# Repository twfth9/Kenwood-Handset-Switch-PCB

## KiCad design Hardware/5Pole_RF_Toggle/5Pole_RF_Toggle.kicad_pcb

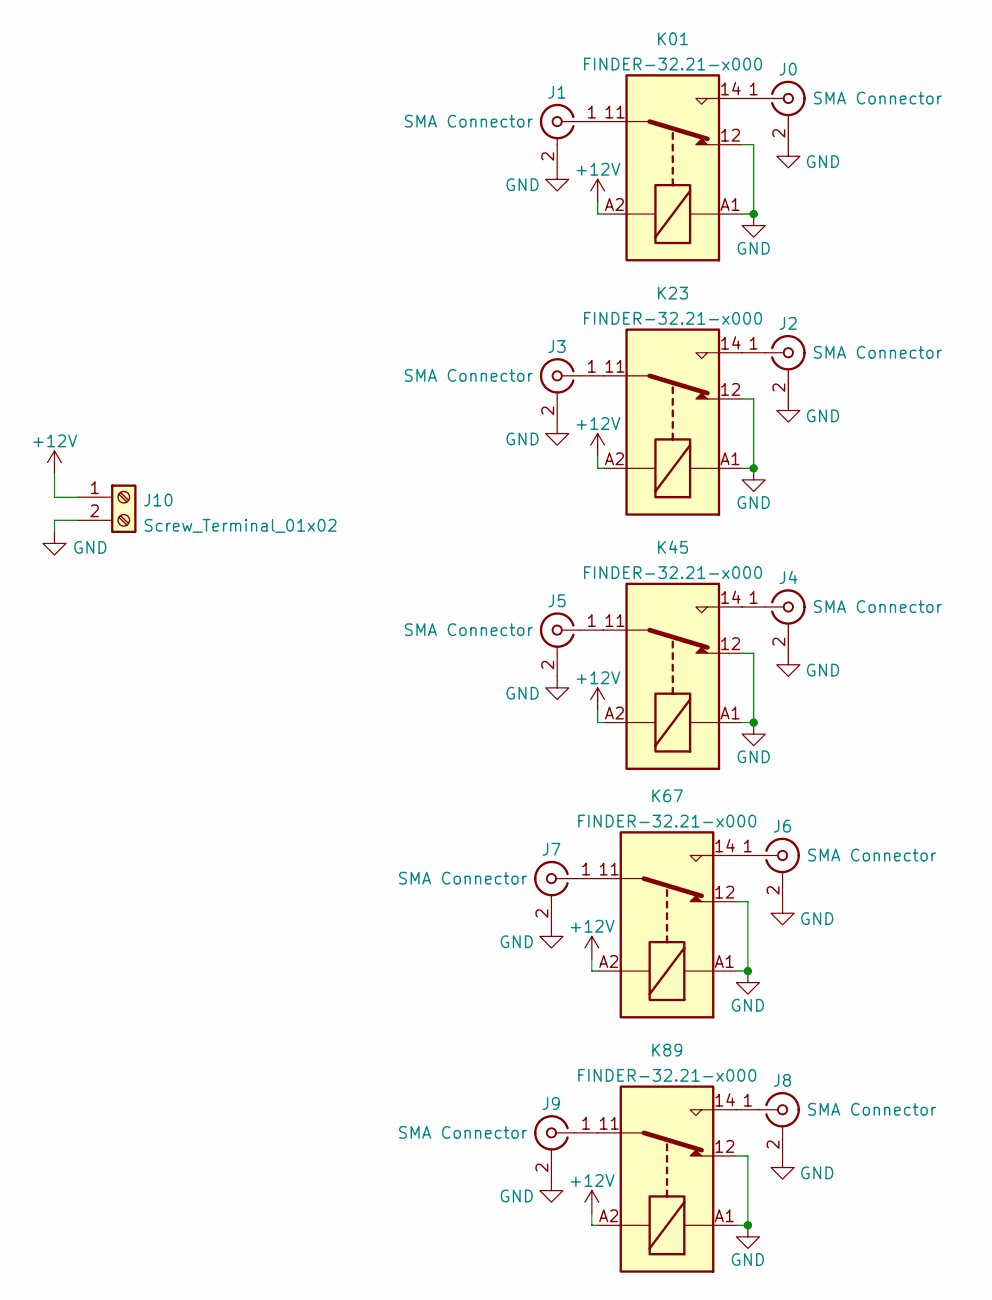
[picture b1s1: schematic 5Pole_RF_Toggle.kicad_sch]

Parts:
J0, J1, J2, J3, J4, J5, J6, J7, J8, J9: SMA Connector; SMA_Amphenol_132134-11_Vertical
J10: Screw_Terminal_01x02; TerminalBlock_Phoenix_MKDS-1,5-2_1x02_P5.00mm_Horizontal
K01, K23, K45, K67, K89: FINDER-32.21-x000; Relay_SPDT_Finder_32.21-x000

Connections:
+12V: J10.1, K01.A2, K23.A2, K45.A2, K67.A2, K89.A2
GND: J0.2 (Ext), J1.2 (Ext), J2.2 (Ext), J3.2 (Ext), J4.2 (Ext), J5.2 (Ext), J6.2 (Ext), J7.2 (Ext), J8.2 (Ext), J9.2 (Ext), J10.2, K01.12, K01.A1, K23.12, K23.A1, K45.12, K45.A1, K67.12, K67.A1, K89.12, K89.A1
unnamed: J0.1 (In), K01.14
unnamed: J1.1 (In), K01.11
unnamed: J2.1 (In), K23.14
unnamed: J3.1 (In), K23.11
unnamed: J4.1 (In), K45.14
unnamed: J5.1 (In), K45.11
unnamed: J6.1 (In), K67.14
unnamed: J7.1 (In), K67.11
unnamed: J8.1 (In), K89.14
unnamed: J9.1 (In), K89.11

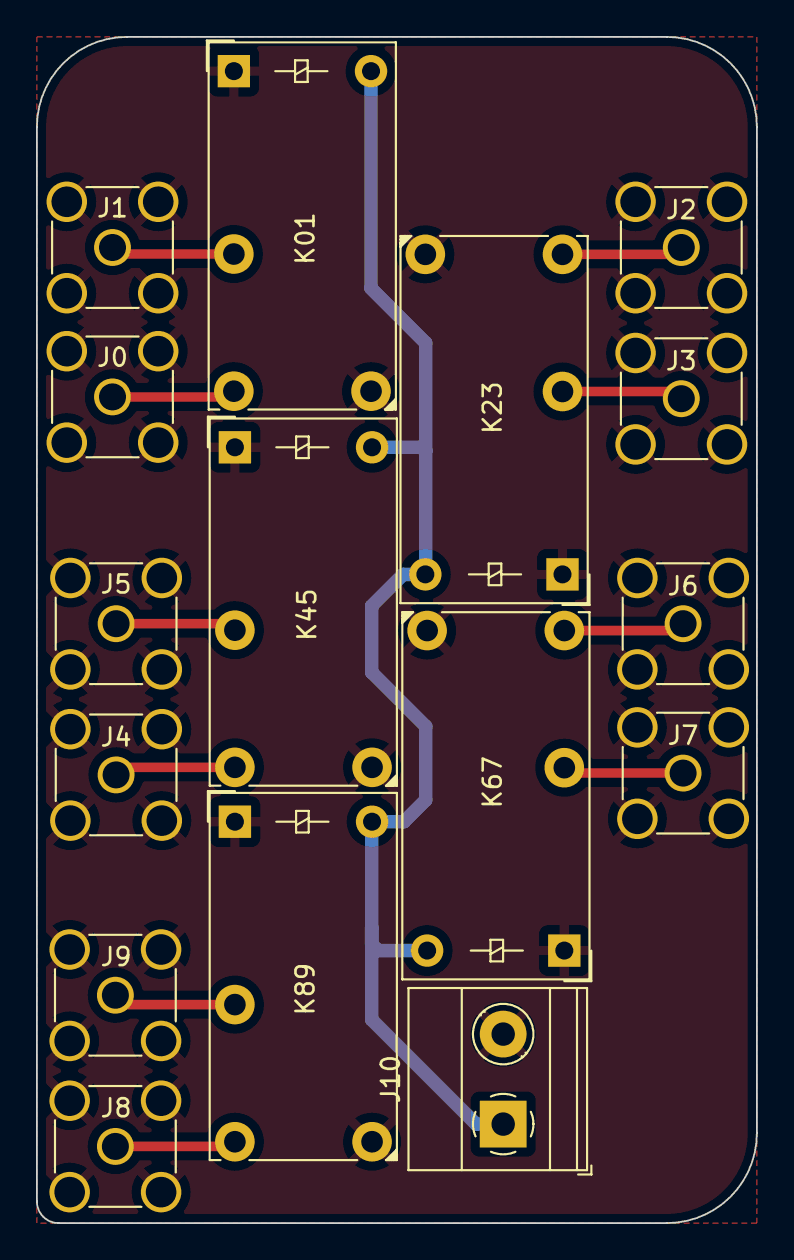
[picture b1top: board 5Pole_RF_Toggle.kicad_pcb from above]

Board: 2 copper layers, 40.0 x 65.9 mm, 16 parts (0 on the bottom side), 12 nets.

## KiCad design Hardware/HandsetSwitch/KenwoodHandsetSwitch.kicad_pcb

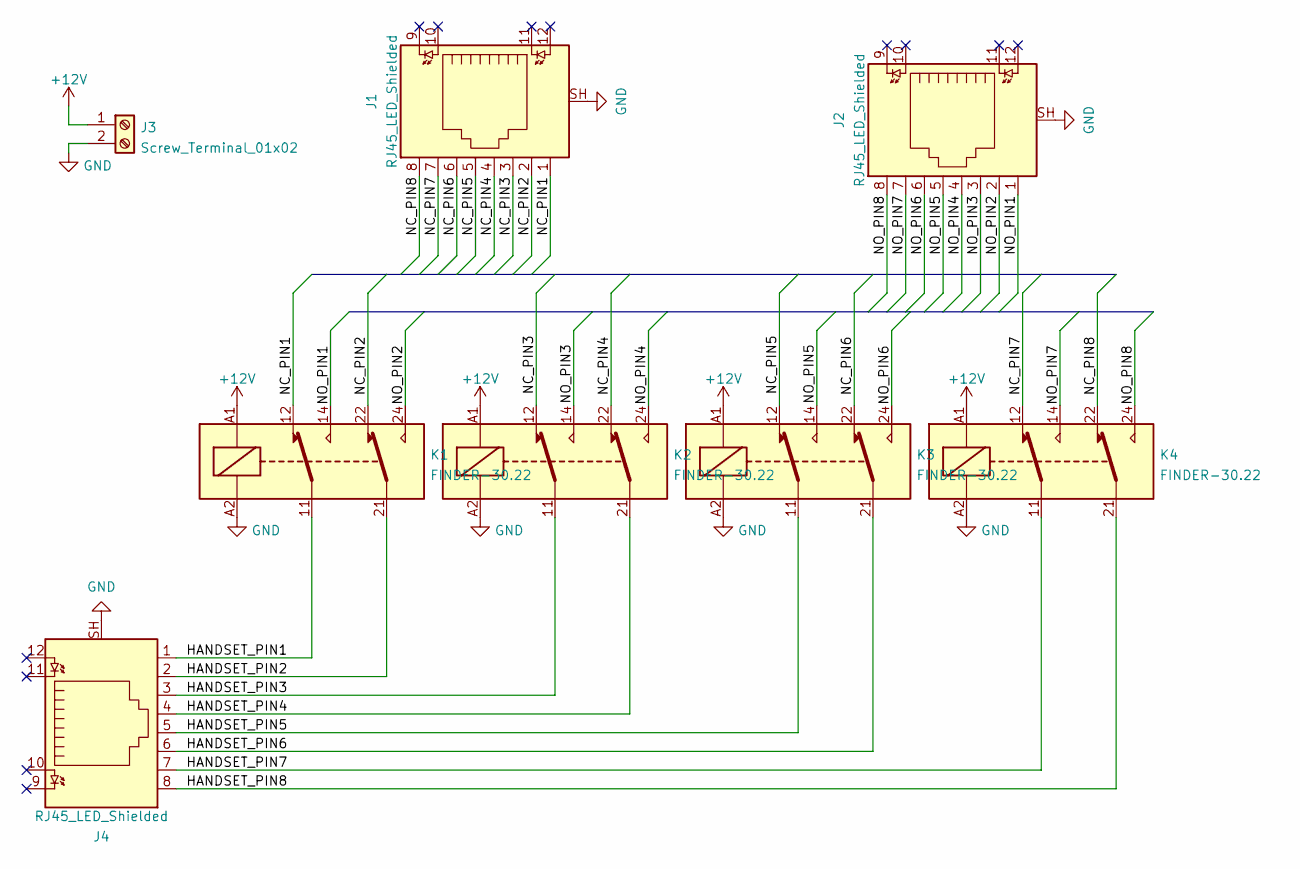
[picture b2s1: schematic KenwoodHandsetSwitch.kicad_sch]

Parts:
J1, J2, J4: RJ45_LED_Shielded; RJ45_BEL_SS74301-00x_Vertical
J3: Screw_Terminal_01x02; TerminalBlock_Phoenix_MKDS-1,5-2_1x02_P5.00mm_Horizontal
K1, K2, K3, K4: FINDER-30.22; Relay_DPDT_Finder_30.22

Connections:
+12V: J3.1, K1.A1, K2.A1, K3.A1, K4.A1
/HANDSET_PIN1: J4.1, K1.11
/HANDSET_PIN2: J4.2, K1.21
/HANDSET_PIN3: J4.3, K2.11
/HANDSET_PIN4: J4.4, K2.21
/HANDSET_PIN5: J4.5, K3.11
/HANDSET_PIN6: J4.6, K3.21
/HANDSET_PIN7: J4.7, K4.11
/HANDSET_PIN8: J4.8, K4.21
/NC_PIN1: J1.1, K1.12
/NC_PIN2: J1.2, K1.22
/NC_PIN3: J1.3, K2.12
/NC_PIN4: J1.4, K2.22
/NC_PIN5: J1.5, K3.12
/NC_PIN6: J1.6, K3.22
/NC_PIN7: J1.7, K4.12
/NC_PIN8: J1.8, K4.22
/NO_PIN1: J2.1, K1.14
/NO_PIN2: J2.2, K1.24
/NO_PIN3: J2.3, K2.14
/NO_PIN4: J2.4, K2.24
/NO_PIN5: J2.5, K3.14
/NO_PIN6: J2.6, K3.24
/NO_PIN7: J2.7, K4.14
/NO_PIN8: J2.8, K4.24
GND: J1.SH, J2.SH, J3.2, J4.SH, K1.A2, K2.A2, K3.A2, K4.A2

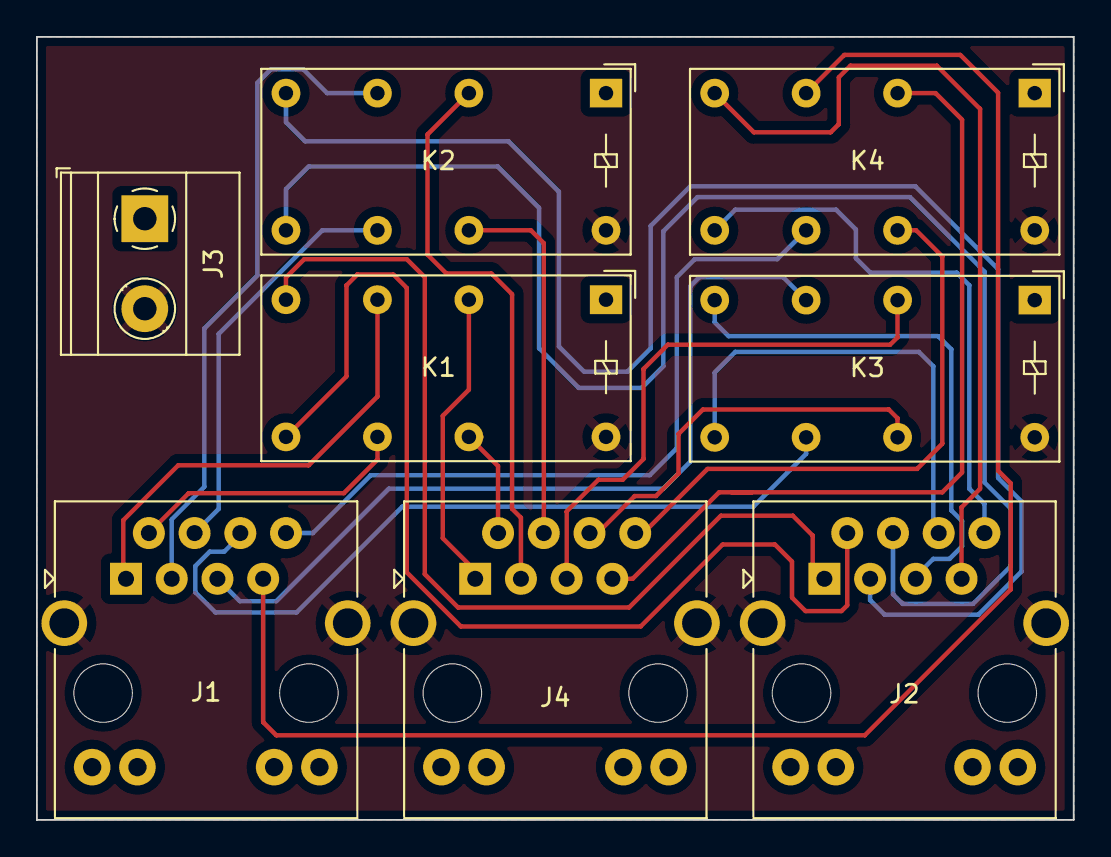
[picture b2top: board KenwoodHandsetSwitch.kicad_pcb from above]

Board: 2 copper layers, 57.6 x 43.5 mm, 8 parts (0 on the bottom side), 26 nets.

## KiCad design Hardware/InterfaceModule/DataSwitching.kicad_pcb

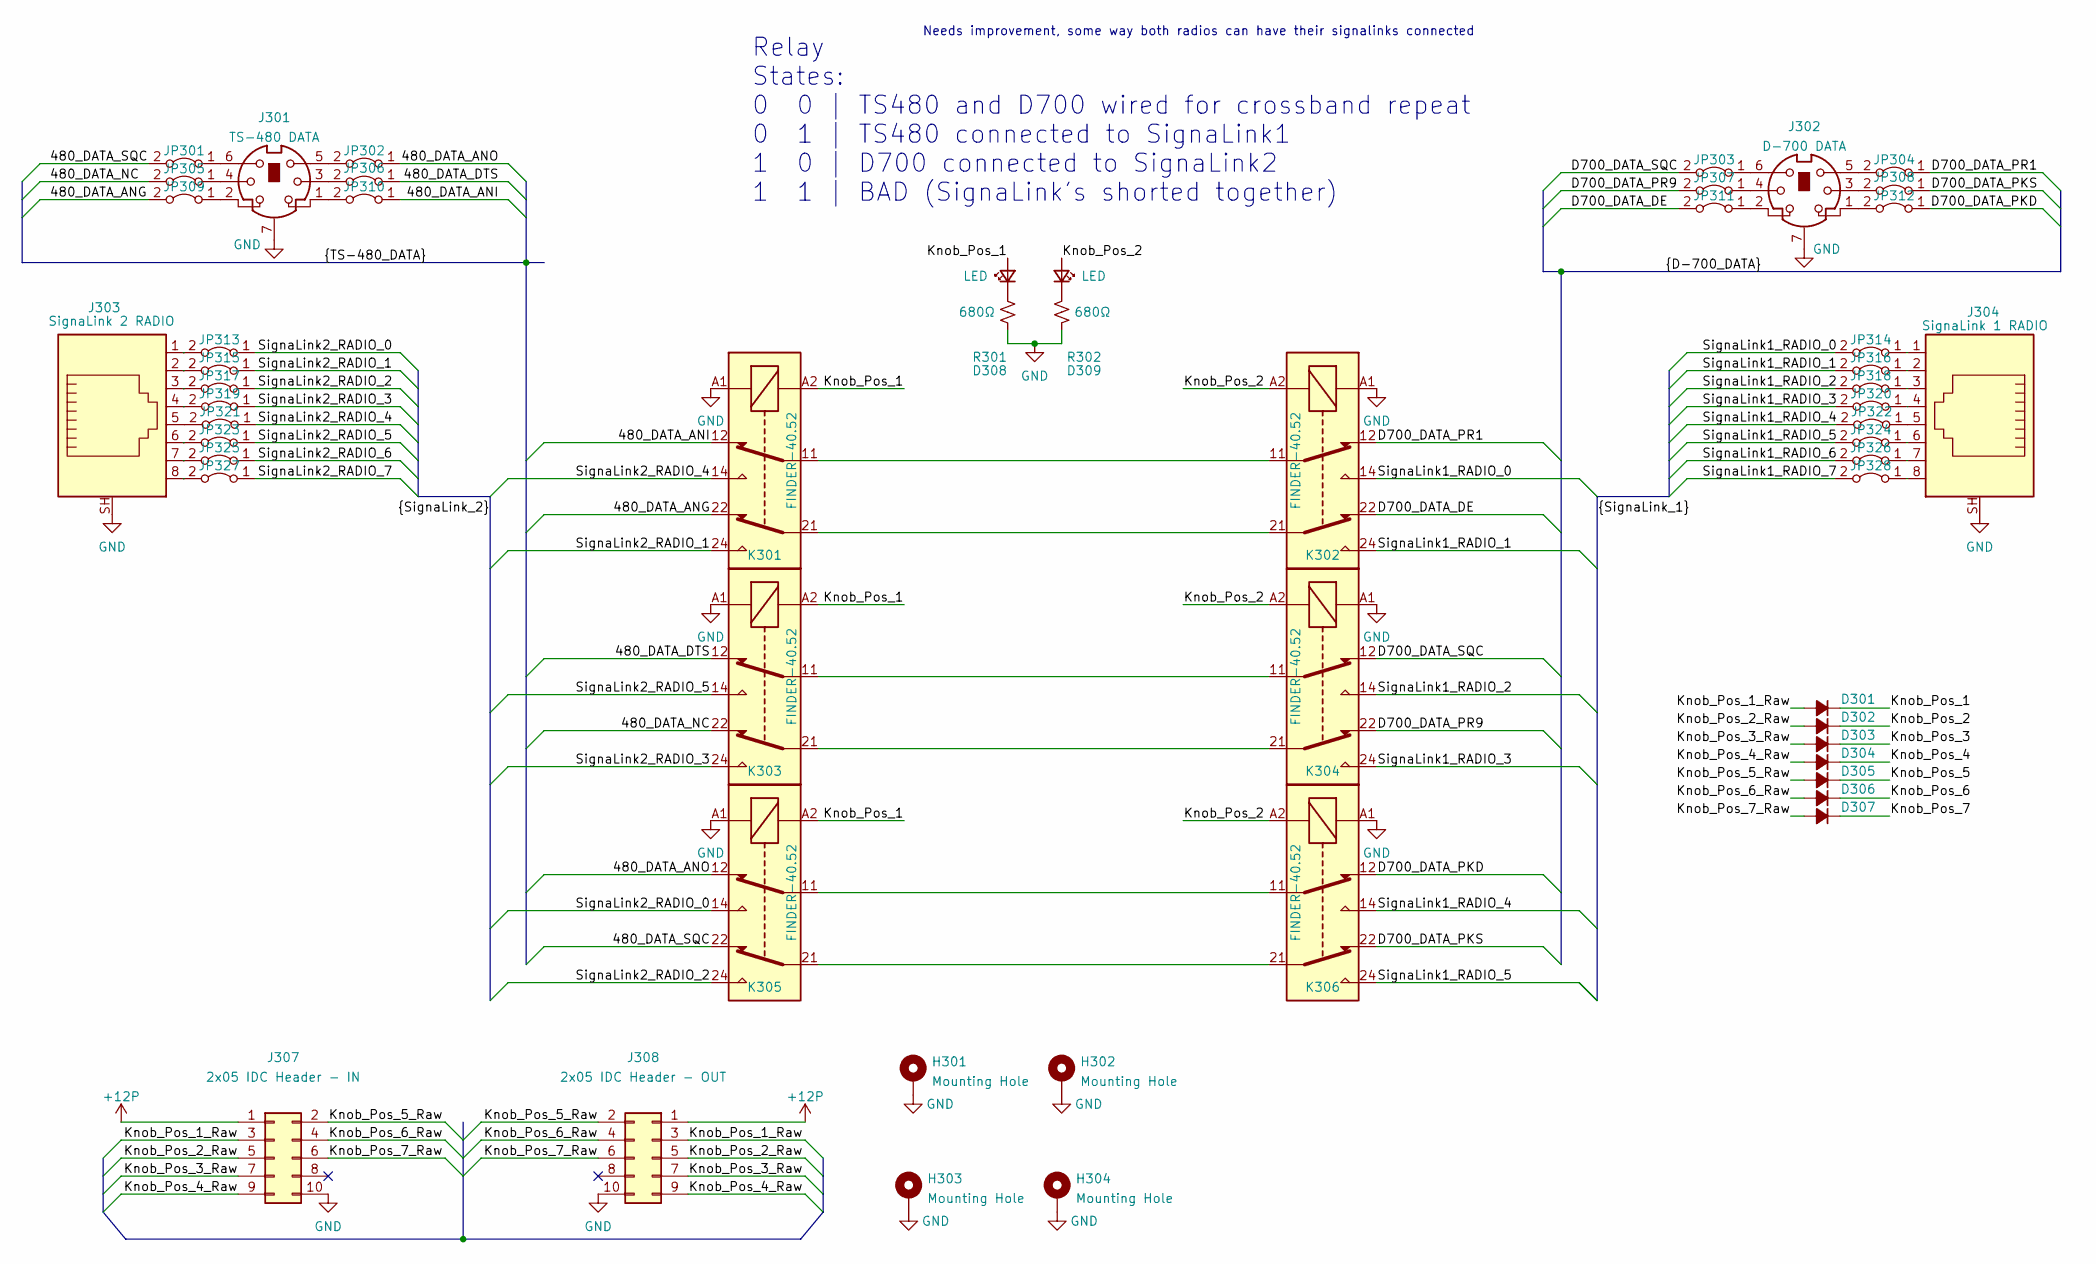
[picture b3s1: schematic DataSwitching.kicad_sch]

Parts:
D301, D302, D303, D304, D305, D306, D307: D_Small_Filled; D_A-405_P2.54mm_Vertical_AnodeUp
D308, D309: LED; LED_D3.0mm
H301, H302, H303, H304: Mounting Hole; M3_Mounting
J301: TS-480 DATA; Connector_Mini-DIN_Female_6Pin_2rows
J302: D-700 DATA; Connector_Mini-DIN_Female_6Pin_2rows
J303: SignaLink 2 RADIO; Mystery_RJ45
J304: SignaLink 1 RADIO; Mystery_RJ45
J307: 2x05 IDC Header - IN; IDC-Header_2x05_P2.54mm_Vertical
J308: 2x05 IDC Header - OUT; IDC-Header_2x05_P2.54mm_Vertical
JP301, JP302, JP303, JP304, JP305, JP306, JP307, JP308, JP309, JP310, JP311, JP312, JP313, JP314, JP315, JP316, JP317, JP318, JP319, JP320, JP321, JP322, JP323, JP324, JP325, JP326, JP327, JP328: Jumper_2_Bridged; 1.0mm_Bridge
K301, K302, K303, K304, K305, K306: FINDER-40.52; Relay_DPDT_Finder_30.22
R301, R302: 680Ω; R_Axial_DIN0207_L6.3mm_D2.5mm_P2.54mm_Vertical

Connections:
+12P: J307.1, J308.1
/Data Port Switching/480_DATA_ANG: JP309.2 (B), K301.22
/Data Port Switching/480_DATA_ANI: JP310.1 (A), K301.12
/Data Port Switching/480_DATA_ANO: JP302.1 (A), K305.12
/Data Port Switching/480_DATA_DTS: JP306.1 (A), K303.12
/Data Port Switching/480_DATA_NC: JP305.2 (B), K303.22
/Data Port Switching/480_DATA_SQC: JP301.2 (B), K305.22
/Data Port Switching/D700_DATA_DE: JP311.2 (B), K302.22
/Data Port Switching/D700_DATA_PKD: JP312.1 (A), K306.12
/Data Port Switching/D700_DATA_PKS: JP308.1 (A), K306.22
/Data Port Switching/D700_DATA_PR1: JP304.1 (A), K302.12
/Data Port Switching/D700_DATA_PR9: JP307.2 (B), K304.22
/Data Port Switching/D700_DATA_SQC: JP303.2 (B), K304.12
/Data Port Switching/Knob_Pos_1: D301.1 (K), D308.2 (A), K301.A2, K303.A2, K305.A2
/Data Port Switching/Knob_Pos_1_Raw: D301.2 (A), J307.3, J308.3
/Data Port Switching/Knob_Pos_2: D302.1 (K), D309.2 (A), K302.A2, K304.A2, K306.A2
/Data Port Switching/Knob_Pos_2_Raw: D302.2 (A), J307.5, J308.5
/Data Port Switching/Knob_Pos_3: D303.1 (K)
/Data Port Switching/Knob_Pos_3_Raw: D303.2 (A), J307.7, J308.7
/Data Port Switching/Knob_Pos_4: D304.1 (K)
/Data Port Switching/Knob_Pos_4_Raw: D304.2 (A), J307.9, J308.9
/Data Port Switching/Knob_Pos_5: D305.1 (K)
/Data Port Switching/Knob_Pos_5_Raw: D305.2 (A), J307.2, J308.2
/Data Port Switching/Knob_Pos_6: D306.1 (K)
/Data Port Switching/Knob_Pos_6_Raw: D306.2 (A), J307.4, J308.4
/Data Port Switching/Knob_Pos_7: D307.1 (K)
/Data Port Switching/Knob_Pos_7_Raw: D307.2 (A), J307.6, J308.6
/Data Port Switching/SignaLink1_RADIO_0: JP314.2 (B), K302.14
/Data Port Switching/SignaLink1_RADIO_1: JP316.2 (B), K302.24
/Data Port Switching/SignaLink1_RADIO_2: JP318.2 (B), K304.14
/Data Port Switching/SignaLink1_RADIO_3: JP320.2 (B), K304.24
/Data Port Switching/SignaLink1_RADIO_4: JP322.2 (B), K306.14
/Data Port Switching/SignaLink1_RADIO_5: JP324.2 (B), K306.24
/Data Port Switching/SignaLink1_RADIO_6: JP326.2 (B)
/Data Port Switching/SignaLink1_RADIO_7: JP328.2 (B)
/Data Port Switching/SignaLink2_RADIO_0: JP313.1 (A), K305.14
/Data Port Switching/SignaLink2_RADIO_1: JP315.1 (A), K301.24
/Data Port Switching/SignaLink2_RADIO_2: JP317.1 (A), K305.24
/Data Port Switching/SignaLink2_RADIO_3: JP319.1 (A), K303.24
/Data Port Switching/SignaLink2_RADIO_4: JP321.1 (A), K301.14
/Data Port Switching/SignaLink2_RADIO_5: JP323.1 (A), K303.14
/Data Port Switching/SignaLink2_RADIO_6: JP325.1 (A)
/Data Port Switching/SignaLink2_RADIO_7: JP327.1 (A)
GND: H301.1, H302.1, H303.1, H304.1, J301.7, J302.7, J303.SH, J304.SH, J307.10, J308.10, K301.A1, K302.A1, K303.A1, K304.A1, K305.A1, K306.A1, R301.2, R302.2
unnamed: D308.1 (K), R301.1
unnamed: D309.1 (K), R302.1
unnamed: J301.1, JP310.2 (B)
unnamed: J301.2, JP309.1 (A)
unnamed: J301.3, JP306.2 (B)
unnamed: J301.4, JP305.1 (A)
unnamed: J301.5, JP302.2 (B)
unnamed: J301.6, JP301.1 (A)
unnamed: J302.1, JP312.2 (B)
unnamed: J302.2, JP311.1 (A)
unnamed: J302.3, JP308.2 (B)
unnamed: J302.4, JP307.1 (A)
unnamed: J302.5, JP304.2 (B)
unnamed: J302.6, JP303.1 (A)
unnamed: J303.1, JP313.2 (B)
unnamed: J303.2, JP315.2 (B)
unnamed: J303.3, JP317.2 (B)
unnamed: J303.4, JP319.2 (B)
unnamed: J303.5, JP321.2 (B)
unnamed: J303.6, JP323.2 (B)
unnamed: J303.7, JP325.2 (B)
unnamed: J303.8, JP327.2 (B)
unnamed: J304.1, JP314.1 (A)
unnamed: J304.2, JP316.1 (A)
unnamed: J304.3, JP318.1 (A)
unnamed: J304.4, JP320.1 (A)
unnamed: J304.5, JP322.1 (A)
unnamed: J304.6, JP324.1 (A)
unnamed: J304.7, JP326.1 (A)
unnamed: J304.8, JP328.1 (A)
unnamed: K301.11, K302.11
unnamed: K301.21, K302.21
unnamed: K303.11, K304.11
unnamed: K303.21, K304.21
unnamed: K305.11, K306.11
unnamed: K305.21, K306.21

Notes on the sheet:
Relay States: 0 0 | TS480 and D700 wired for crossband repeat 0 1 | TS480 connected to SignaLink1 1 0 | D700 connected to SignaLink2 1 1 | BAD (SignaLink's shorted together)
Needs improvement, some way both radios can have their signalinks connected

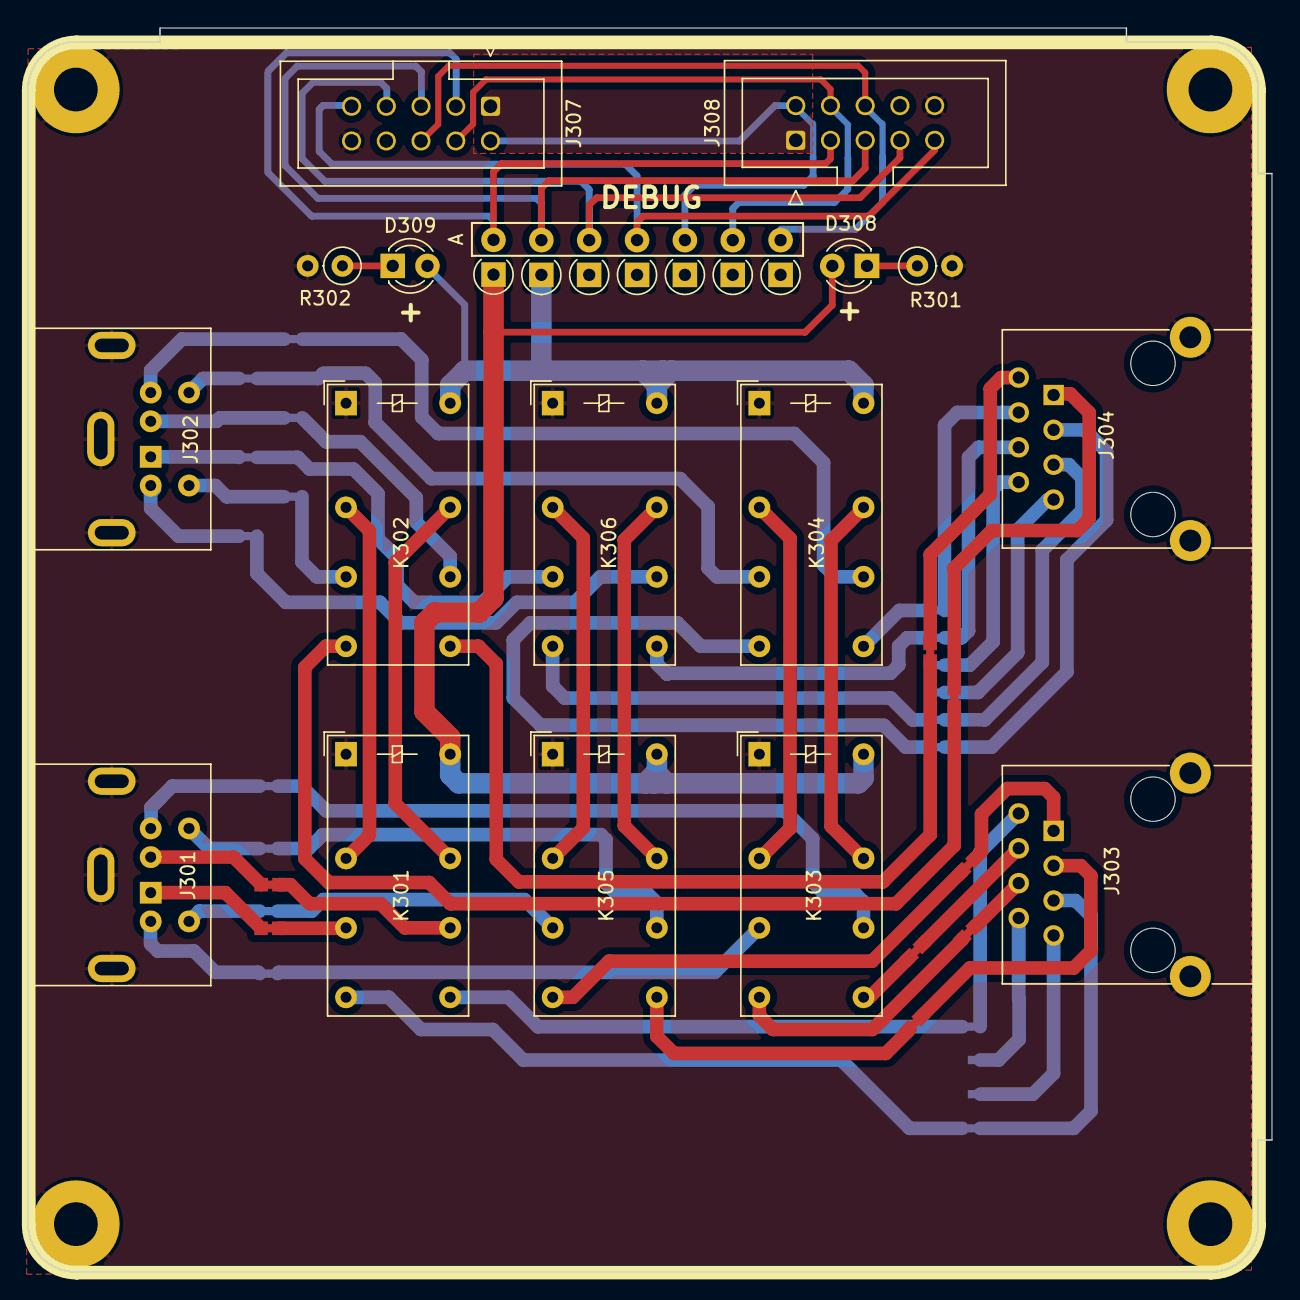
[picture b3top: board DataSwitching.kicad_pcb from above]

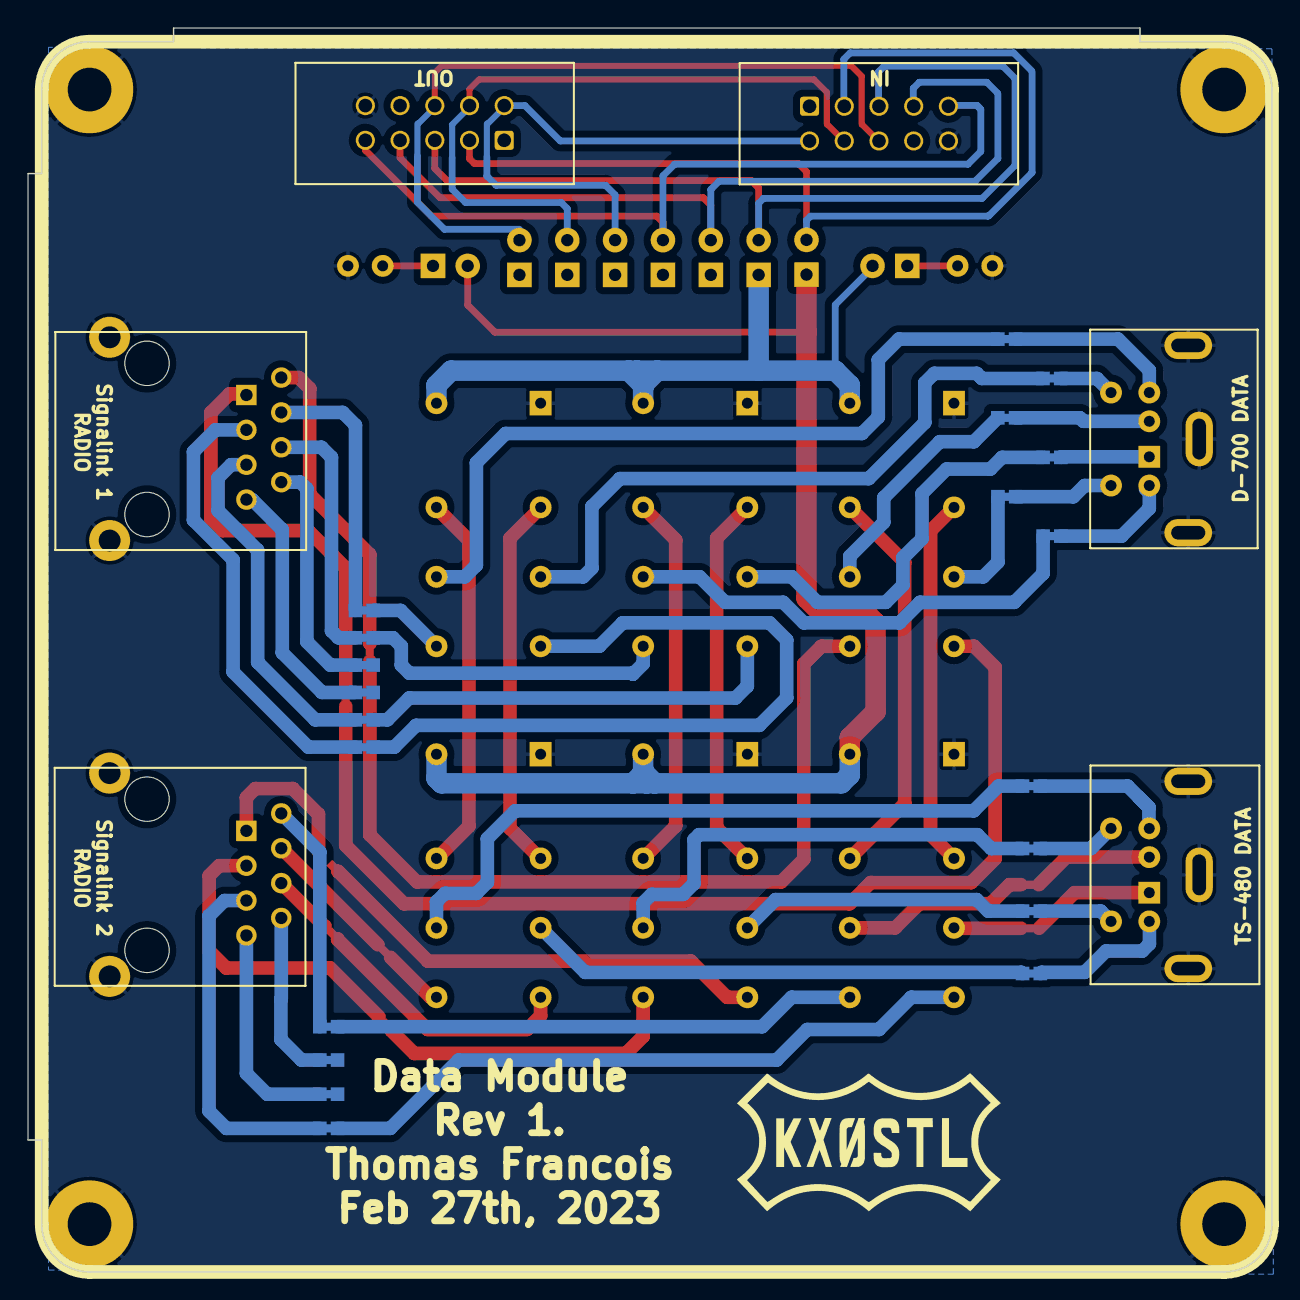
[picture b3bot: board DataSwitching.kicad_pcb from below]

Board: 2 copper layers, 91.0 x 91.0 mm, 55 parts (20 on the bottom side), 71 nets.

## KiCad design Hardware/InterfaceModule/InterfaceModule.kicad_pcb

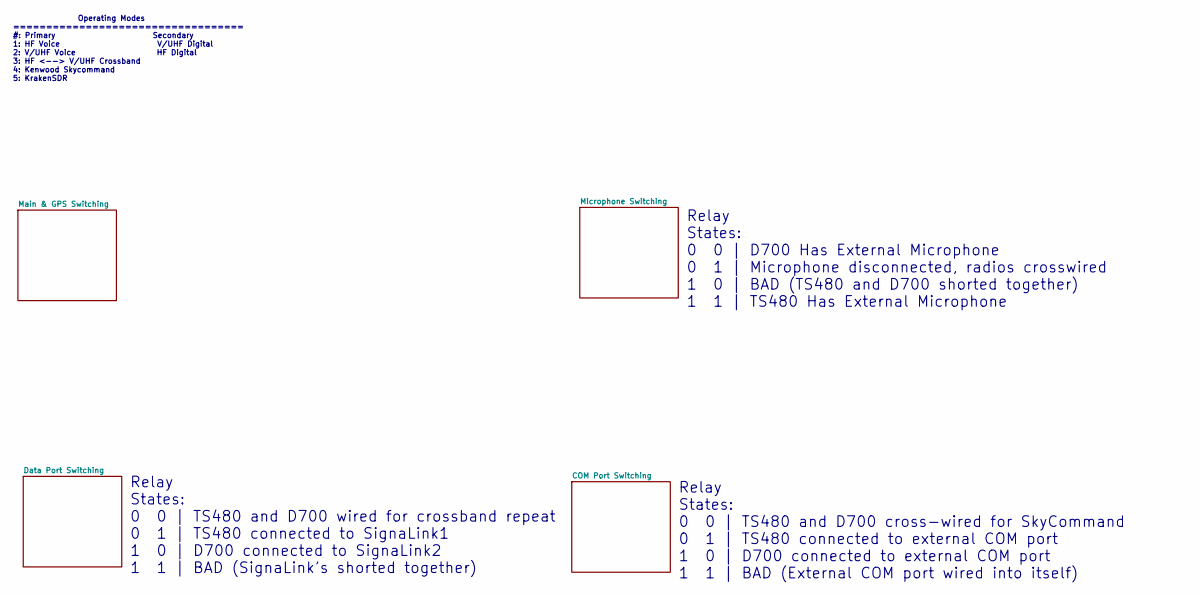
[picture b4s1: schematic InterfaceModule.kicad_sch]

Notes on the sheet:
Relay States: 0 0 | TS480 and D700 cross-wired for SkyCommand 0 1 | TS480 connected to external COM port 1 0 | D700 connected to external COM port 1 1 | BAD (External COM port wired into itself)
Relay States: 0 0 | TS480 and D700 wired for crossband repeat 0 1 | TS480 connected to SignaLink1 1 0 | D700 connected to SignaLink2 1 1 | BAD (SignaLink's shorted together)
Operating Modes =================================== #: Primary Secondary 1: HF Voice V/UHF Digital 2: V/UHF Voice HF Digital 3: HF <--> V/UHF Crossband 4: Kenwood Skycommand 5: KrakenSDR
Relay States: 0 0 | D700 Has External Microphone 0 1 | Microphone disconnected, radios crosswired 1 0 | BAD (TS480 and D700 shorted together) 1 1 | TS480 Has External Microphone

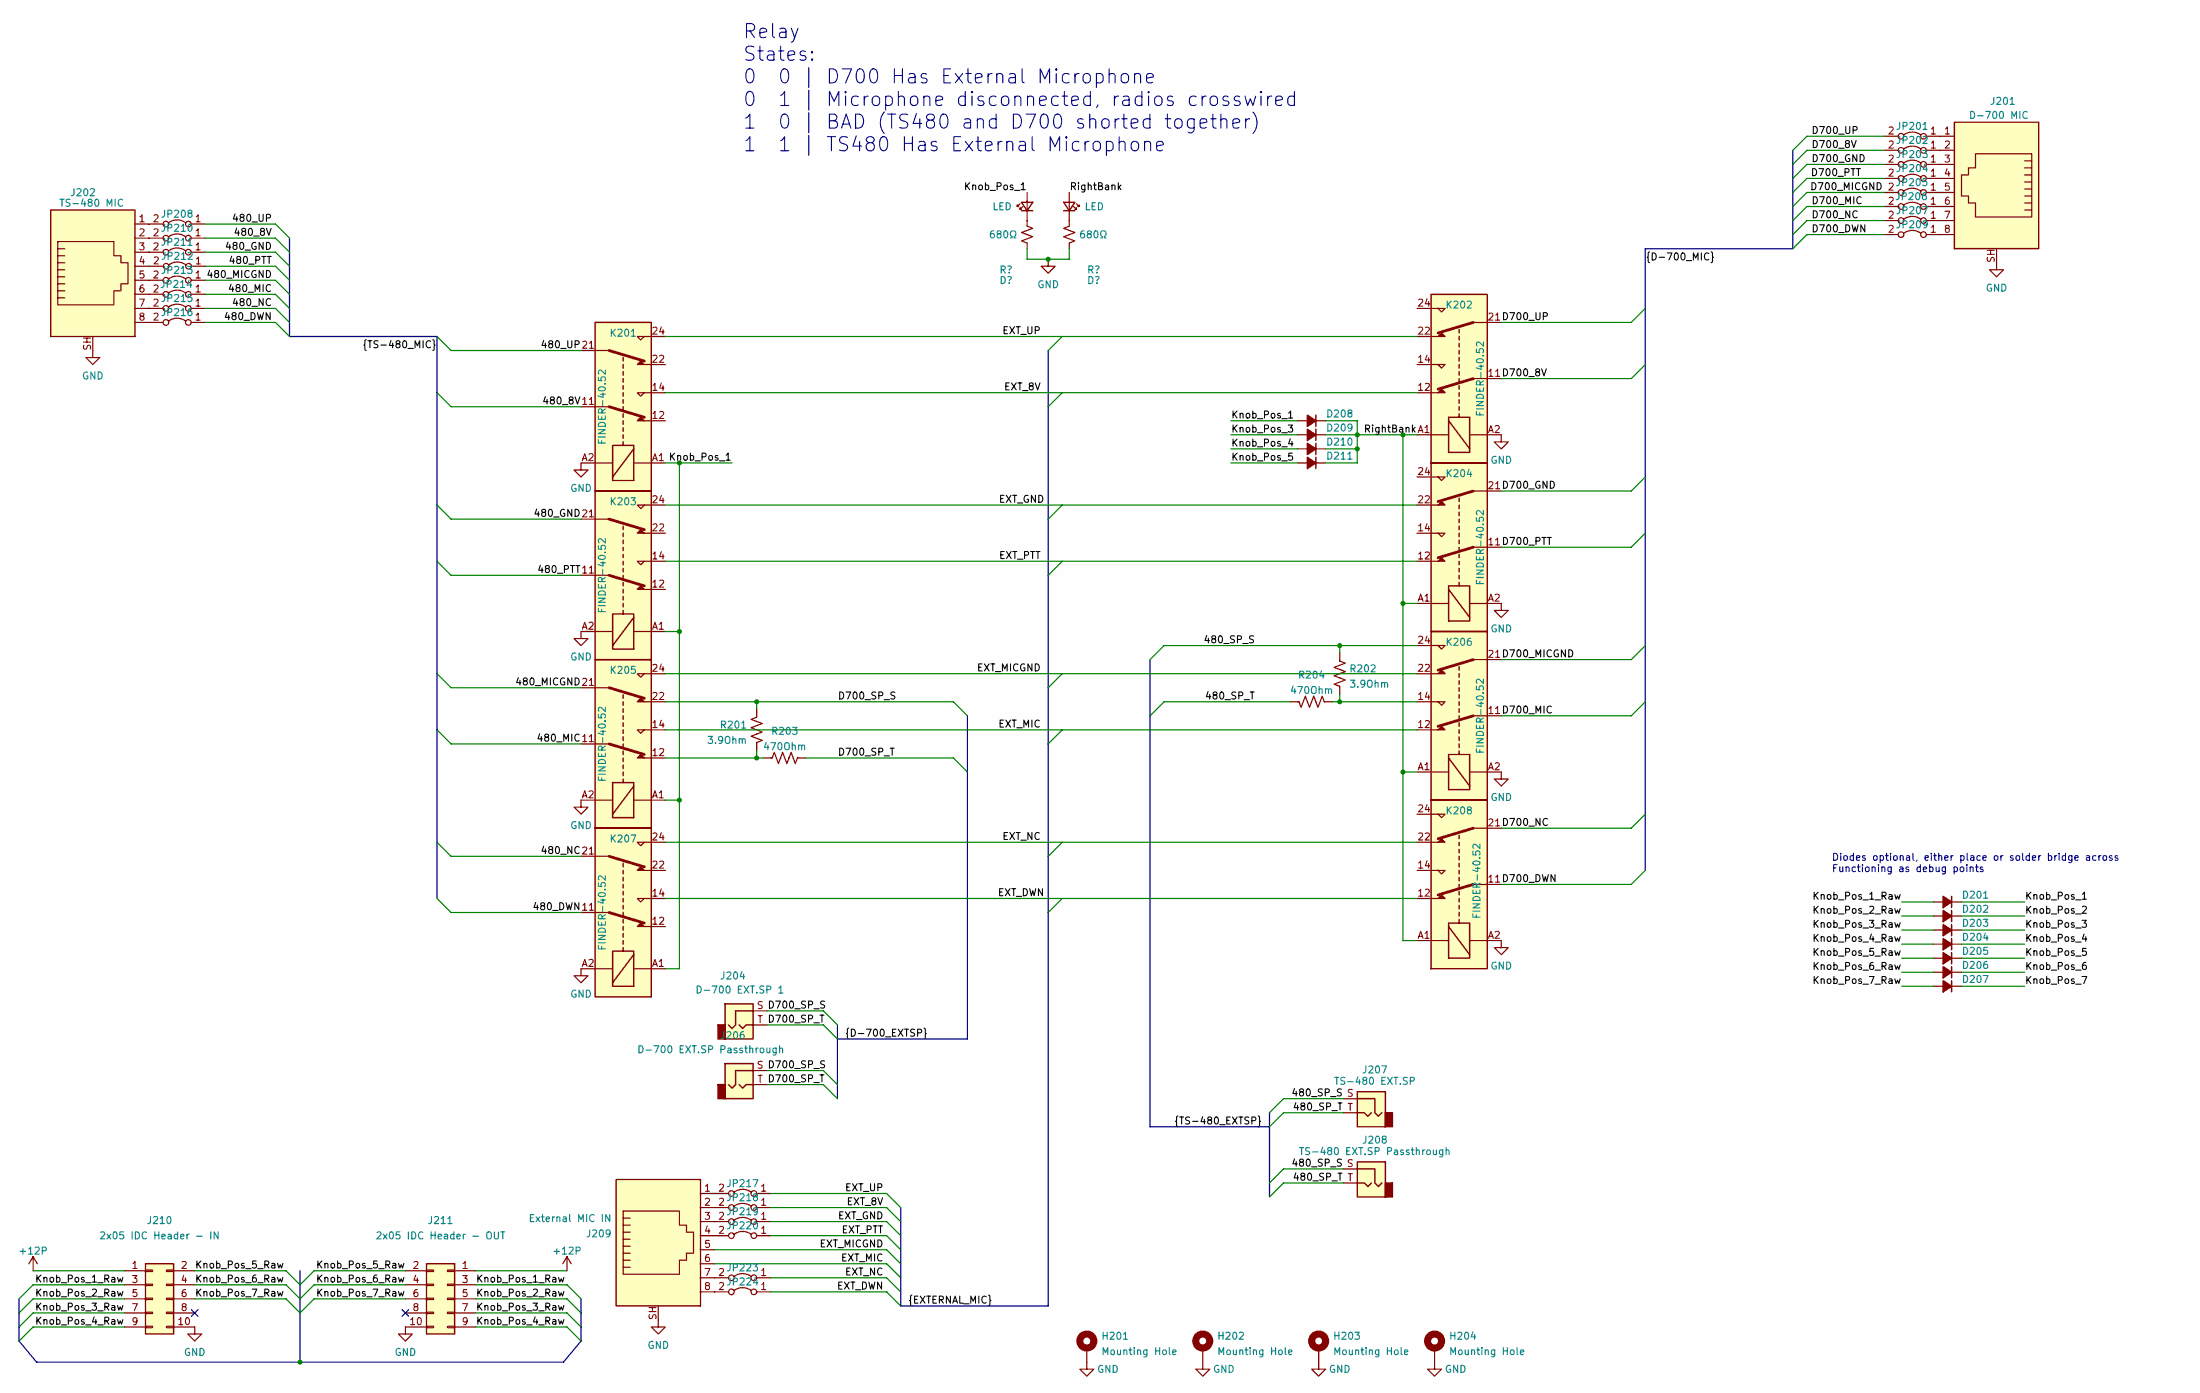
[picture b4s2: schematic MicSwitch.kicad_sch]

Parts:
D201, D202, D203, D204, D205, D206, D207, D208, D209, D210, D211: D_Small_Filled; D_A-405_P2.54mm_Vertical_AnodeUp
H201, H202, H203, H204: Mounting Hole; M3_Mounting
J201: D-700 MIC; Mystery_RJ45
J202: TS-480 MIC; Mystery_RJ45
J204: D-700 EXT.SP 1; Mystery_3.5mm
J206: D-700 EXT.SP Passthrough; Mystery_3.5mm
J207: TS-480 EXT.SP; Mystery_3.5mm
J208: TS-480 EXT.SP Passthrough; Mystery_3.5mm
J209: External MIC IN; Mystery_RJ45
J210: 2x05 IDC Header - IN; IDC-Header_2x05_P2.54mm_Vertical
J211: 2x05 IDC Header - OUT; IDC-Header_2x05_P2.54mm_Vertical
JP201, JP202, JP203, JP204, JP205, JP206, JP207, JP208, JP209, JP210, JP211, JP212, JP213, JP214, JP215, JP216, JP217, JP218, JP219, JP220, JP223, JP224: Jumper_2_Bridged; 1.0mm_Bridge
K201, K202, K203, K204, K205, K206, K207, K208: FINDER-40.52; Relay_DPDT_Finder_30.22
R201, R202: 3.9Ohm; R_Axial_DIN0207_L6.3mm_D2.5mm_P2.54mm_Vertical
R203, R204: 470Ohm; R_Axial_DIN0207_L6.3mm_D2.5mm_P2.54mm_Vertical

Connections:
+12P: J210.1, J211.1; also elsewhere on the board
/Microphone Switching/480_8V: JP210.1 (A), K201.11
/Microphone Switching/480_DWN: JP216.1 (A), K207.11
/Microphone Switching/480_GND: JP211.1 (A), K203.21
/Microphone Switching/480_MIC: JP214.1 (A), K205.11
/Microphone Switching/480_MICGND: JP213.1 (A), K205.21
/Microphone Switching/480_NC: JP215.1 (A), K207.21
/Microphone Switching/480_PTT: JP212.1 (A), K203.11
/Microphone Switching/480_SP_S: J207.S, J208.S, K206.24, R202.1
/Microphone Switching/480_SP_T: J207.T, J208.T, R204.1
/Microphone Switching/480_UP: JP208.1 (A), K201.21
/Microphone Switching/D700_8V: JP202.2 (B), K202.11
/Microphone Switching/D700_DWN: JP209.2 (B), K208.11
/Microphone Switching/D700_GND: JP203.2 (B), K204.21
/Microphone Switching/D700_MIC: JP206.2 (B), K206.11
/Microphone Switching/D700_MICGND: JP205.2 (B), K206.21
/Microphone Switching/D700_NC: JP207.2 (B), K208.21
/Microphone Switching/D700_PTT: JP204.2 (B), K204.11
/Microphone Switching/D700_SP_S: J204.S, J206.S, K205.22, R201.1
/Microphone Switching/D700_SP_T: J204.T, J206.T, R203.1
/Microphone Switching/D700_UP: JP201.2 (B), K202.21
/Microphone Switching/EXT_8V: JP218.1 (A), K201.14, K202.12
/Microphone Switching/EXT_DWN: JP224.1 (A), K207.14, K208.12
/Microphone Switching/EXT_GND: JP219.1 (A), K203.24, K204.22
/Microphone Switching/EXT_MIC: J209.6, K205.14, K206.12
/Microphone Switching/EXT_MICGND: J209.5, K205.24, K206.22
/Microphone Switching/EXT_NC: JP223.1 (A), K207.24, K208.22
/Microphone Switching/EXT_PTT: JP220.1 (A), K203.14, K204.12
/Microphone Switching/EXT_UP: JP217.1 (A), K201.24, K202.22
/Microphone Switching/Knob_Pos_1: D201.1 (K), D208.2 (A), K201.A1, K203.A1, K205.A1, K207.A1
/Microphone Switching/Knob_Pos_1_Raw: D201.2 (A), J210.3, J211.3
/Microphone Switching/Knob_Pos_2: D202.1 (K)
/Microphone Switching/Knob_Pos_2_Raw: D202.2 (A), J210.5, J211.5
/Microphone Switching/Knob_Pos_3: D203.1 (K), D209.2 (A)
/Microphone Switching/Knob_Pos_3_Raw: D203.2 (A), J210.7, J211.7
/Microphone Switching/Knob_Pos_4: D204.1 (K), D210.2 (A)
/Microphone Switching/Knob_Pos_4_Raw: D204.2 (A), J210.9, J211.9
/Microphone Switching/Knob_Pos_5: D205.1 (K), D211.2 (A)
/Microphone Switching/Knob_Pos_5_Raw: D205.2 (A), J210.2, J211.2
/Microphone Switching/Knob_Pos_6: D206.1 (K)
/Microphone Switching/Knob_Pos_6_Raw: D206.2 (A), J210.4, J211.4
/Microphone Switching/Knob_Pos_7: D207.1 (K)
/Microphone Switching/Knob_Pos_7_Raw: D207.2 (A), J210.6, J211.6
/Microphone Switching/RightBank: D208.1 (K), D209.1 (K), D210.1 (K), D211.1 (K), K202.A1, K204.A1, K206.A1, K208.A1
GND: H201.1, H202.1, H203.1, H204.1, J201.SH, J202.SH, J209.SH, J210.10, J211.10, K201.A2, K202.A2, K203.A2, K204.A2, K205.A2, K206.A2, K207.A2, K208.A2; also elsewhere on the board
unnamed: J201.1, JP201.1 (A)
unnamed: J201.2, JP202.1 (A)
unnamed: J201.3, JP203.1 (A)
unnamed: J201.4, JP204.1 (A)
unnamed: J201.5, JP205.1 (A)
unnamed: J201.6, JP206.1 (A)
unnamed: J201.7, JP207.1 (A)
unnamed: J201.8, JP209.1 (A)
unnamed: J202.1, JP208.2 (B)
unnamed: J202.2, JP210.2 (B)
unnamed: J202.3, JP211.2 (B)
unnamed: J202.5, JP213.2 (B)
unnamed: J202.6, JP214.2 (B)
unnamed: J202.7, JP215.2 (B)
unnamed: J202.8, JP216.2 (B)
unnamed: J209.1, JP217.2 (B)
unnamed: J209.2, JP218.2 (B)
unnamed: J209.3, JP219.2 (B)
unnamed: J209.4, JP220.2 (B)
unnamed: J209.7, JP223.2 (B)
unnamed: J209.8, JP224.2 (B)
unnamed: J202.4, JP212.2 (B)
unnamed: K205.12, R201.2, R203.2
unnamed: K206.14, R202.2, R204.2

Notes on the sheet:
Relay States: 0 0 | D700 Has External Microphone 0 1 | Microphone disconnected, radios crosswired 1 0 | BAD (TS480 and D700 shorted together) 1 1 | TS480 Has External Microphone
Diodes optional, either place or solder bridge across Functioning as debug points
